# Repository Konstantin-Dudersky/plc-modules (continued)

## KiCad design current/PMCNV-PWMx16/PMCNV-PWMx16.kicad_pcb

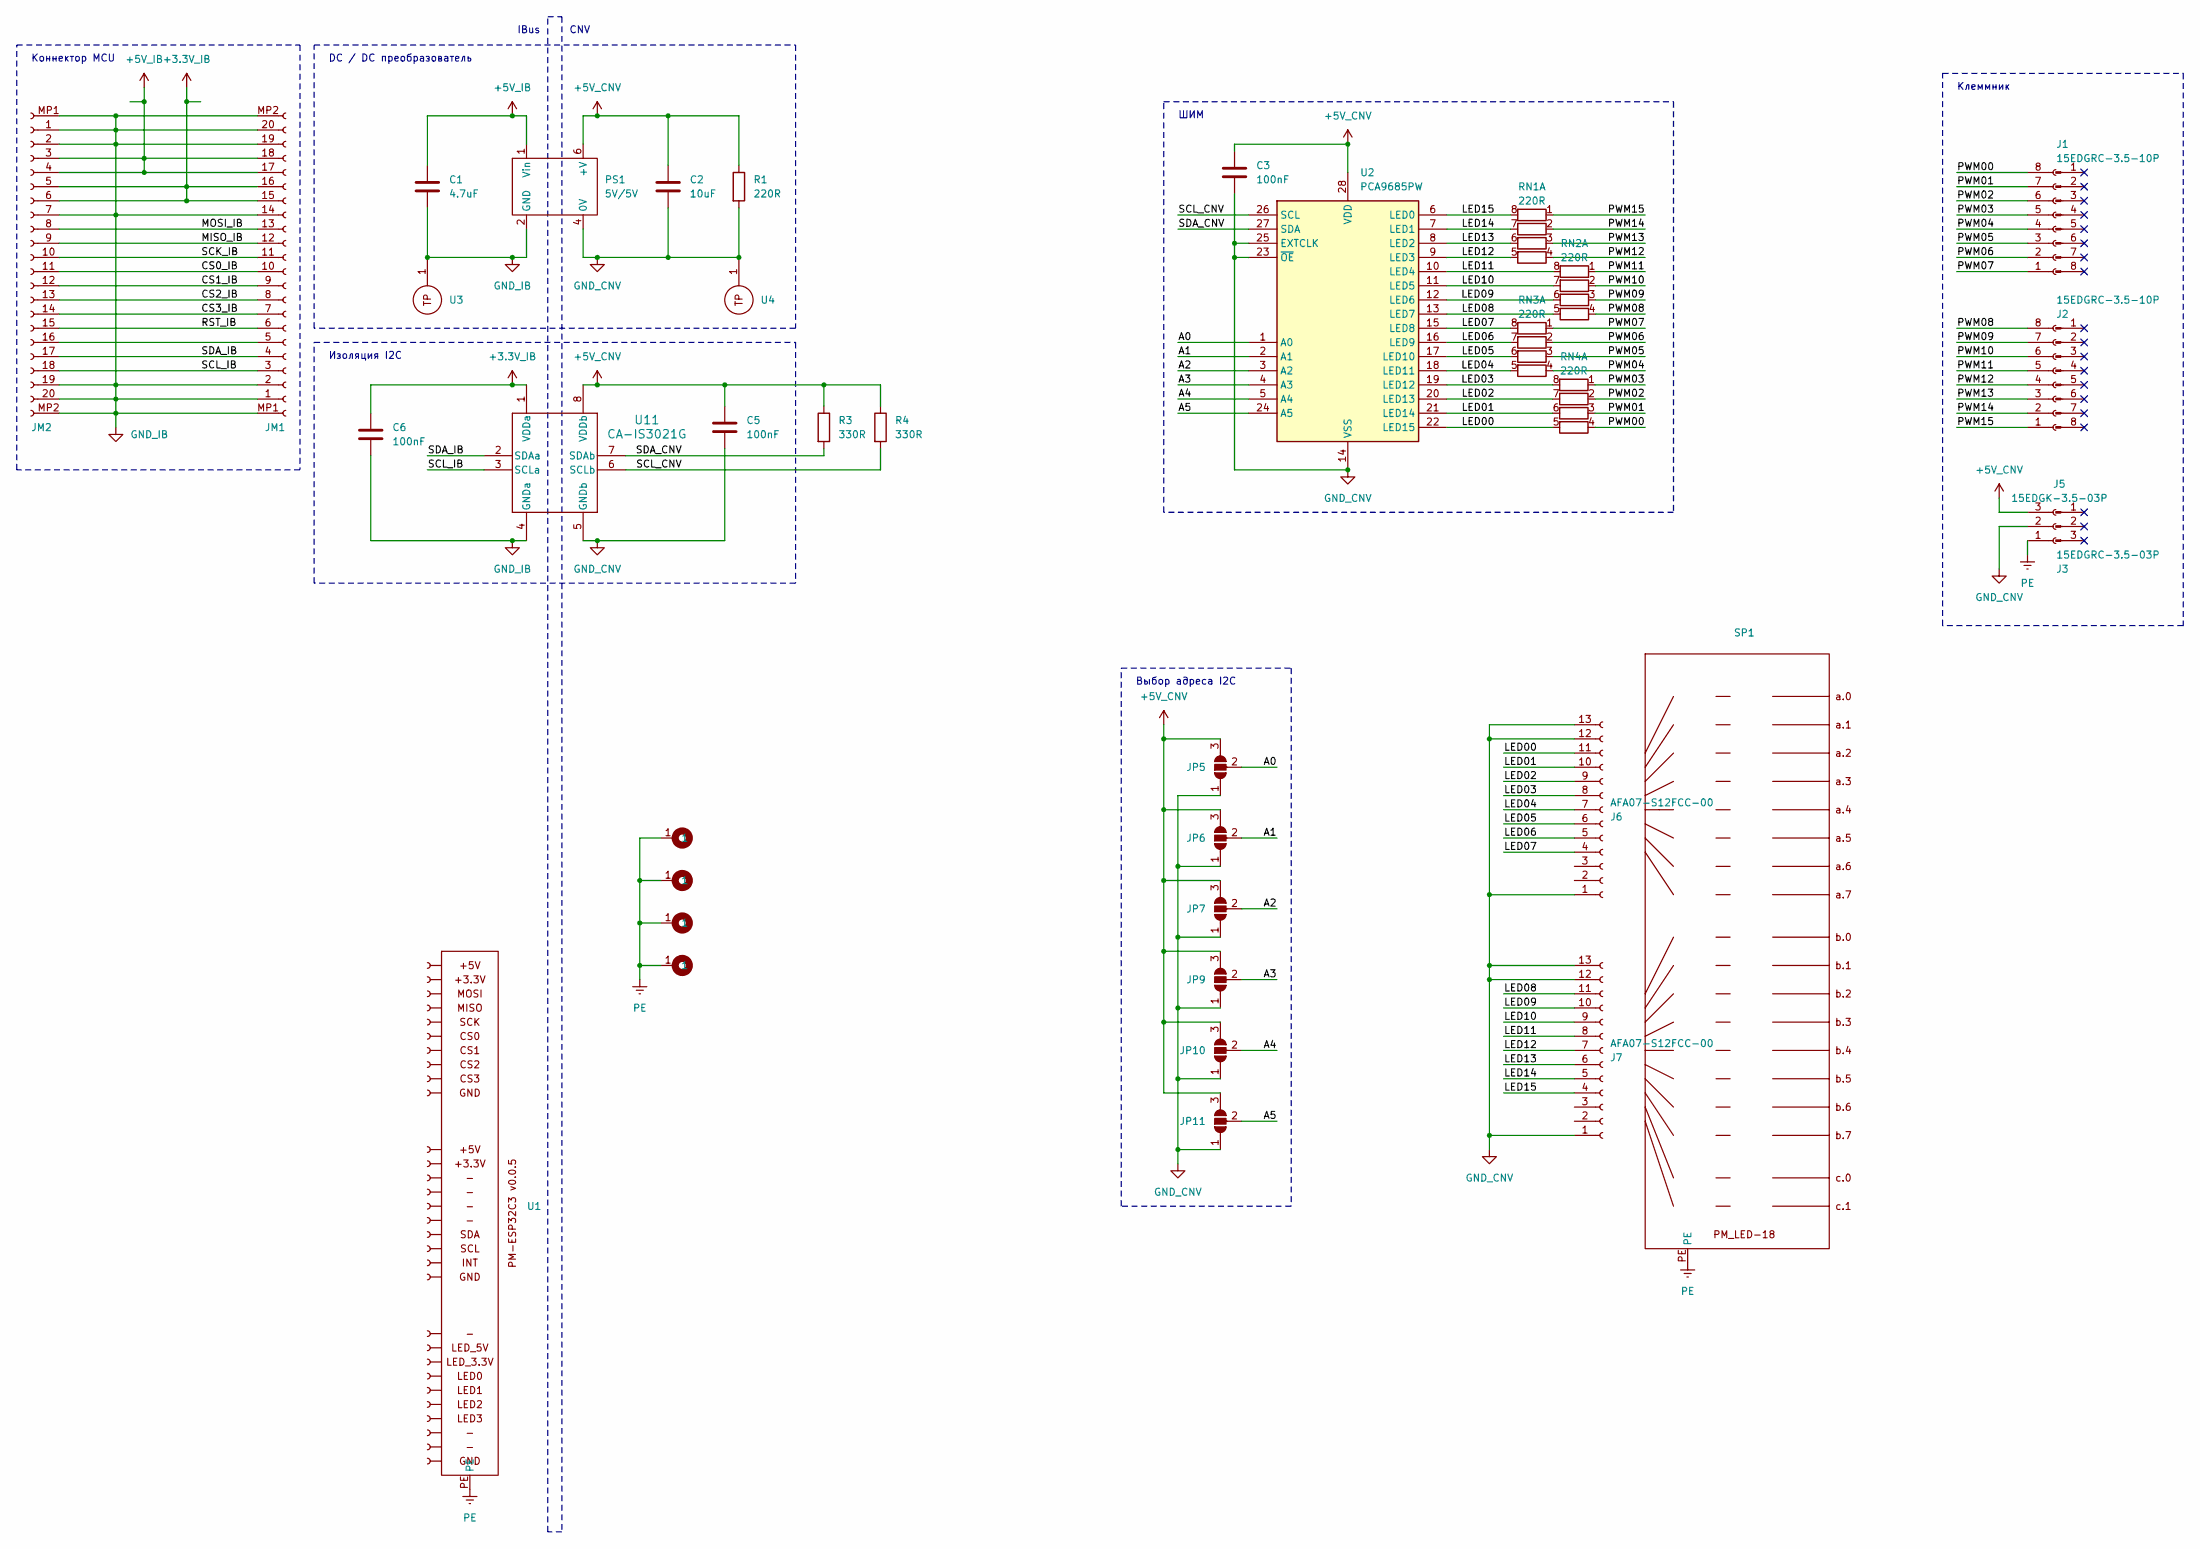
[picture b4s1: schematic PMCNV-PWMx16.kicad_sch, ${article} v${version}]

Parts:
C1: 4.7uF; C_0805_2012Metric; part_ipn C_4.7uF_16V_0805_MLCC-X7R
C2: 10uF; C_0805_2012Metric; part_ipn C_10uF_16V_0805_MLCC-X7R
C3, C5, C6: 100nF; C_0603_1608Metric; part_ipn C_100nF_16V_0603_MLCC-X7R
H1, H2, H3, H4: M4; MountingHole_4.3mm_M4_Pad_Via
J1, J2: 15EDGRC-3.5-10P; 15EDGRC-3.5-08P; part_ipn 15EDGRC-3.5-08P
J3: 15EDGRC-3.5-03P; part_ipn 15EDGRC-3.5-03P
J4, J9: 15EDGK-3.5-10P; part_ipn 15EDGK-3.5-08P
J5: 15EDGK-3.5-03P; part_ipn 15EDGK-3.5-03P
J6, J7: AFA07-S12FCC-00; CONN10_AFA07-S12_JUS; part_ipn AFA07-S12FCC-00
JM1, JM2: AFA07-S20FCC-00; AFA07S20FCA00; part_ipn AFA07-S20FCC-00
JP5, JP6, JP7, JP9, JP10, JP11: SolderJumper_3_Open; SolderJumper-3_P1.3mm_Open_Pad1.0x1.5mm
PS1: 5V/5V; B2405LS-1WR3; part_ipn B0505LS-1W
R1: 220R; R_0603_1608Metric; part_ipn R_220R_0603_1%
R3, R4: 330R; R_0603_1608Metric; part_ipn R_330R_0603_1%
RN1, RN2, RN3, RN4: 220R; R_Array_Convex_4x0603; part_ipn R_220R_0603x4_1%
SP1: PMLED-xx-v0.0.2; part_ipn PMLED-18-v0.0.2
U1: PM-ESP32C3_v0.0.7; part_ipn PM_MCU-ESP32_C3-v0.0.7
U2: PCA9685PW; TSSOP-28_4.4x9.7mm_P0.65mm; part_ipn PCA9685PW
U3, U4: 5117; part_ipn Keystone_5117
U11: CA-IS3021G; SOICW8_CLG; part_ipn CA-IS3021G

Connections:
+3.3V_IB: C6.1, JM1.15 (Pin_11), JM1.16 (Pin_11), JM2.5, JM2.6, U11.1 (VDDa)
+5V_CNV: C2.1, C3.1, C5.1, J3.3, JP5.3 (B), JP6.3 (B), JP7.3 (B), JP9.3 (B), JP10.3 (B), JP11.3 (B), PS1.6 (+V), R1.1, R3.1, R4.1, U2.28 (VDD), U11.8 (VDDb)
+5V_IB: C1.1, JM1.17 (Pin_11), JM1.18 (Pin_11), JM2.3, JM2.4, PS1.1 (Vin)
/A0: JP5.2 (C), U2.1 (A0)
/A1: JP6.2 (C), U2.2 (A1)
/A2: JP7.2 (C), U2.3 (A2)
/A3: JP9.2 (C), U2.4 (A3)
/A4: JP10.2 (C), U2.5 (A4)
/A5: JP11.2 (C), U2.24 (A5)
/CS0_IB: JM1.10, JM2.11
/CS1_IB: JM1.9, JM2.12 (Pin_11)
/CS2_IB: JM1.8, JM2.13 (Pin_11)
/CS3_IB: JM1.7, JM2.14 (Pin_11)
/LED00: J6.11, RN4.5 (R4.2), U2.22 (LED15)
/LED01: J6.10, RN4.6 (R3.2), U2.21 (LED14)
/LED02: J6.9, RN4.7 (R2.2), U2.20 (LED13)
/LED03: J6.8, RN4.8 (R1.2), U2.19 (LED12)
/LED04: J6.7, RN3.5 (R4.2), U2.18 (LED11)
/LED05: J6.6, RN3.6 (R3.2), U2.17 (LED10)
/LED06: J6.5, RN3.7 (R2.2), U2.16 (LED9)
/LED07: J6.4, RN3.8 (R1.2), U2.15 (LED8)
/LED08: J7.11, RN2.5 (R4.2), U2.13 (LED7)
/LED09: J7.10, RN2.6 (R3.2), U2.12 (LED6)
/LED10: J7.9, RN2.7 (R2.2), U2.11 (LED5)
/LED11: J7.8, RN2.8 (R1.2), U2.10 (LED4)
/LED12: J7.7, RN1.5 (R4.2), U2.9 (LED3)
/LED13: J7.6, RN1.6 (R3.2), U2.8 (LED2)
/LED14: J7.5, RN1.7 (R2.2), U2.7 (LED1)
/LED15: J7.4, RN1.8 (R1.2), U2.6 (LED0)
/MISO_IB: JM1.12 (Pin_11), JM2.9
/MOSI_IB: JM1.13 (Pin_11), JM2.8
/PWM00: J1.8, RN4.4 (R4.1)
/PWM01: J1.7, RN4.3 (R3.1)
/PWM02: J1.6, RN4.2 (R2.1)
/PWM03: J1.5, RN4.1 (R1.1)
/PWM04: J1.4, RN3.4 (R4.1)
/PWM05: J1.3, RN3.3 (R3.1)
/PWM06: J1.2, RN3.2 (R2.1)
/PWM07: J1.1, RN3.1 (R1.1)
/PWM08: J2.8, RN2.4 (R4.1)
/PWM09: J2.7, RN2.3 (R3.1)
/PWM10: J2.6, RN2.2 (R2.1)
/PWM11: J2.5, RN2.1 (R1.1)
/PWM12: J2.4, RN1.4 (R4.1)
/PWM13: J2.3, RN1.3 (R3.1)
/PWM14: J2.2, RN1.2 (R2.1)
/PWM15: J2.1, RN1.1 (R1.1)
/RST_IB: JM1.6, JM2.15 (Pin_11)
/SCK_IB: JM1.11, JM2.10
/SCL_CNV: R4.2, U2.26 (SCL), U11.6 (SCLb)
/SCL_IB: JM1.3, JM2.18 (Pin_11), U11.3 (SCLa)
/SDA_CNV: R3.2, U2.27 (SDA), U11.7 (SDAb)
/SDA_IB: JM1.4, JM2.17 (Pin_11), U11.2 (SDAa)
GND_CNV: C2.2, C3.2, C5.2, J3.2, J6.1, J6.12 (Pin_11), J6.13 (Pin_11), J7.1, J7.12 (Pin_11), J7.13 (Pin_11), JP5.1 (A), JP6.1 (A), JP7.1 (A), JP9.1 (A), JP10.1 (A), JP11.1 (A), PS1.4 (0V), R1.2, U2.14 (VSS), U2.23 (~OE), U2.25 (EXTCLK), U4.1, U11.5 (GNDb)
GND_IB: C1.2, C6.2, JM1.1, JM1.2, JM1.14 (Pin_11), JM1.19 (Pin_11), JM1.20 (Pin_11), JM1.MP1 (Pin_11), JM1.MP2 (Pin_11), JM2.1, JM2.2, JM2.7, JM2.19 (Pin_11), JM2.20 (Pin_11), JM2.MP1 (Pin_11), JM2.MP2 (Pin_11), PS1.2 (GND), U3.1, U11.4 (GNDa)
unnamed: JM1.5, JM2.16 (Pin_11)
PE: H1.1, H2.1, H3.1, H4.1, J3.1, SP1.PE, U1.PE

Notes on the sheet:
ШИМ
IBus
DC / DC преобразователь
Клеммник
Выбор адреса I2C
CNV
Коннектор MCU
Изоляция I2C

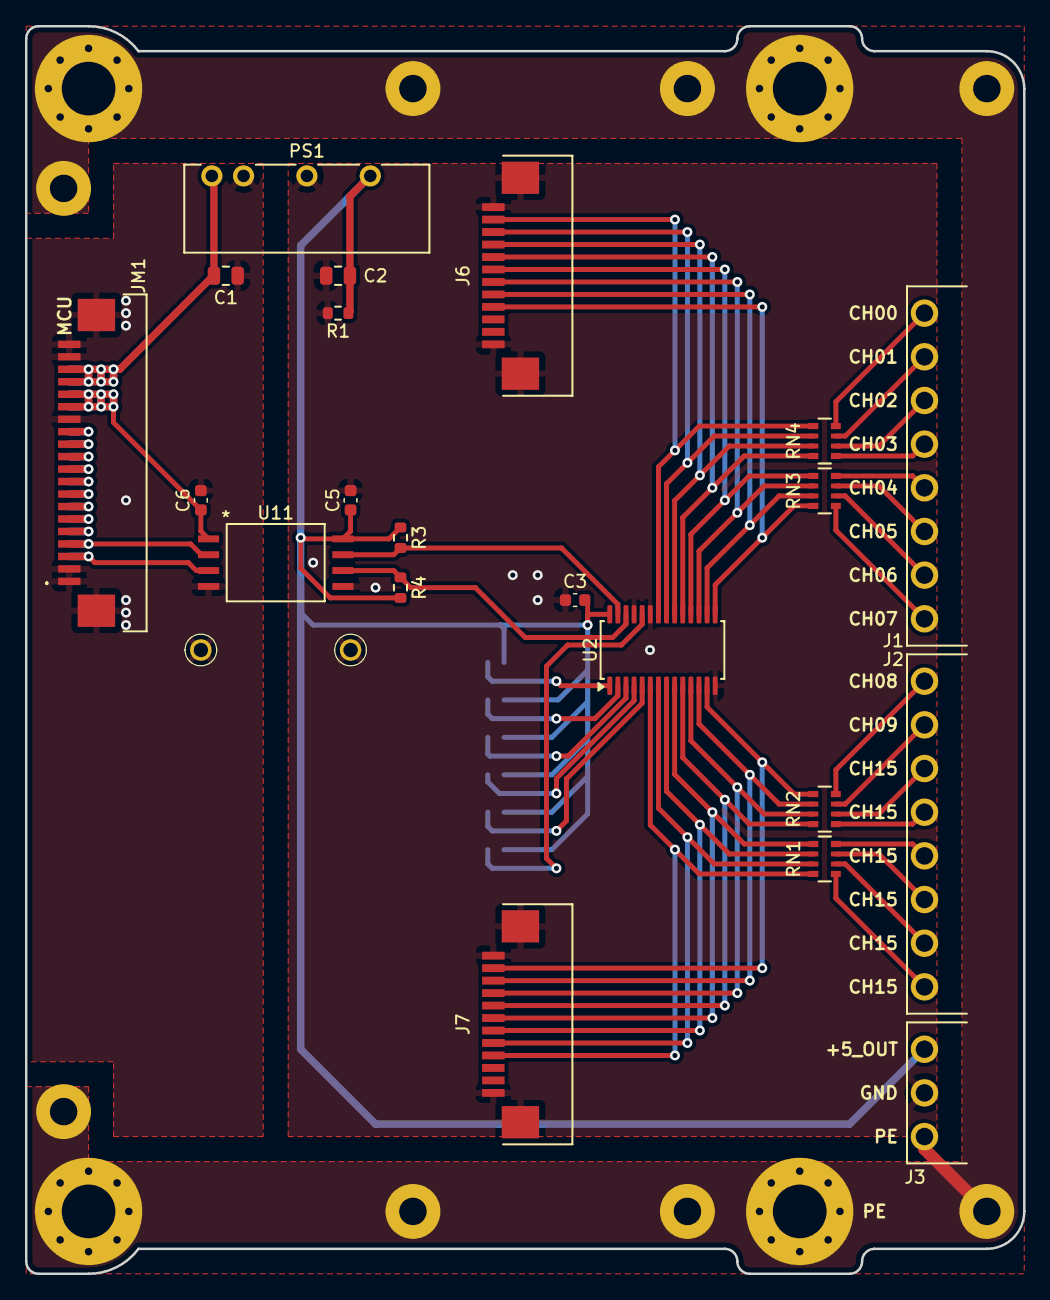
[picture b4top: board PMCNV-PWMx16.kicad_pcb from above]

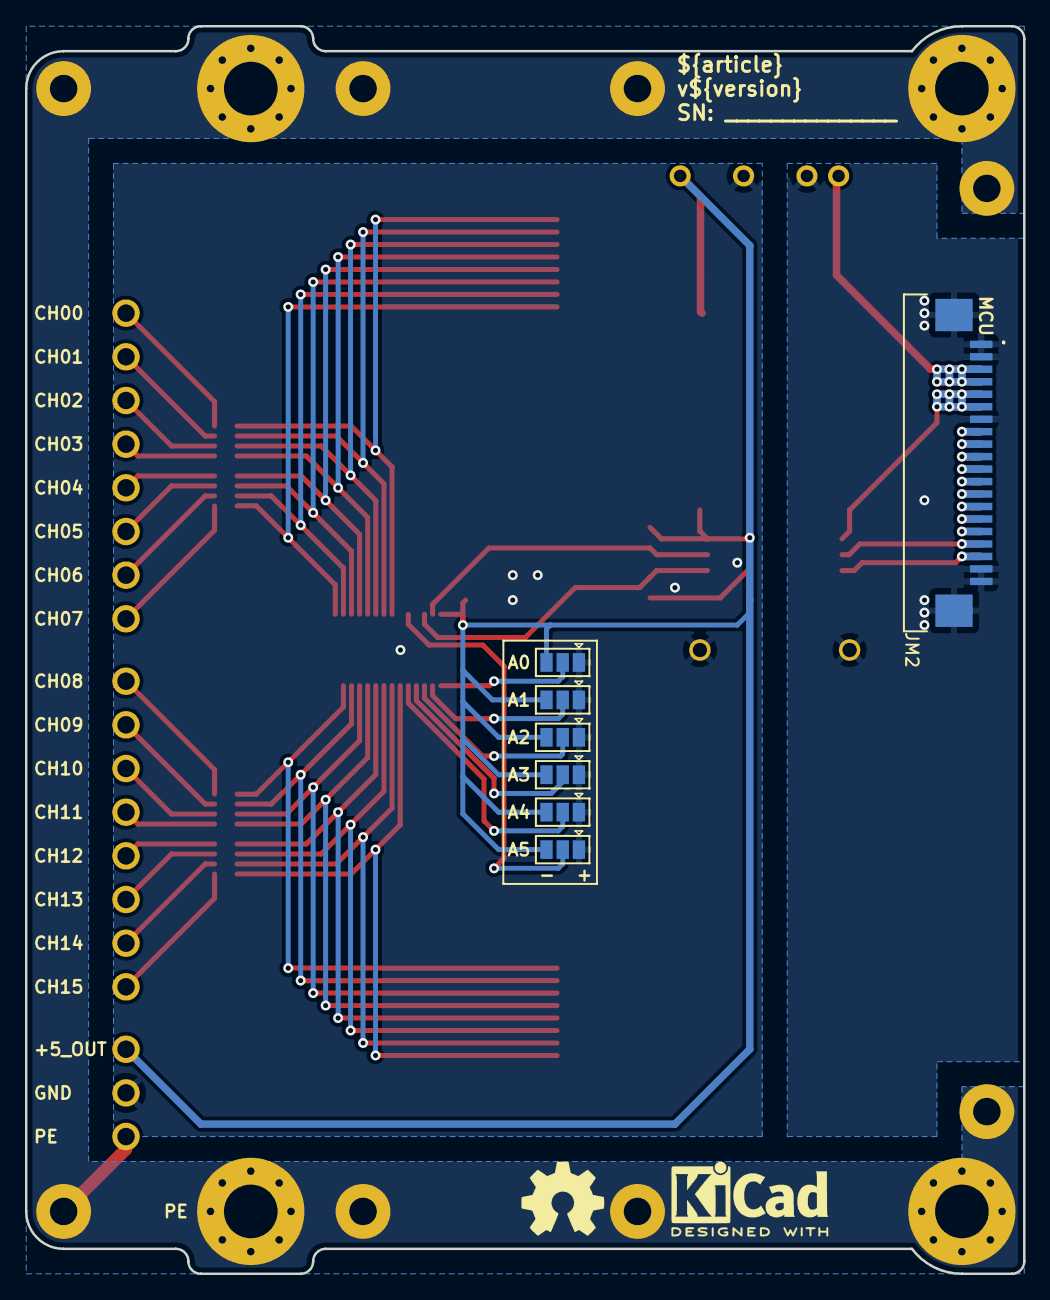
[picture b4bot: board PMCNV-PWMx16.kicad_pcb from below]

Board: 2 copper layers, 80.0 x 100.0 mm, 38 parts (9 on the bottom side), 57 nets.

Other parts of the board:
kicad_logo: KiCad-Logo2_5mm_SilkScreen
oshw_logo: OSHW-Symbol_6.7x6mm_SilkScreen

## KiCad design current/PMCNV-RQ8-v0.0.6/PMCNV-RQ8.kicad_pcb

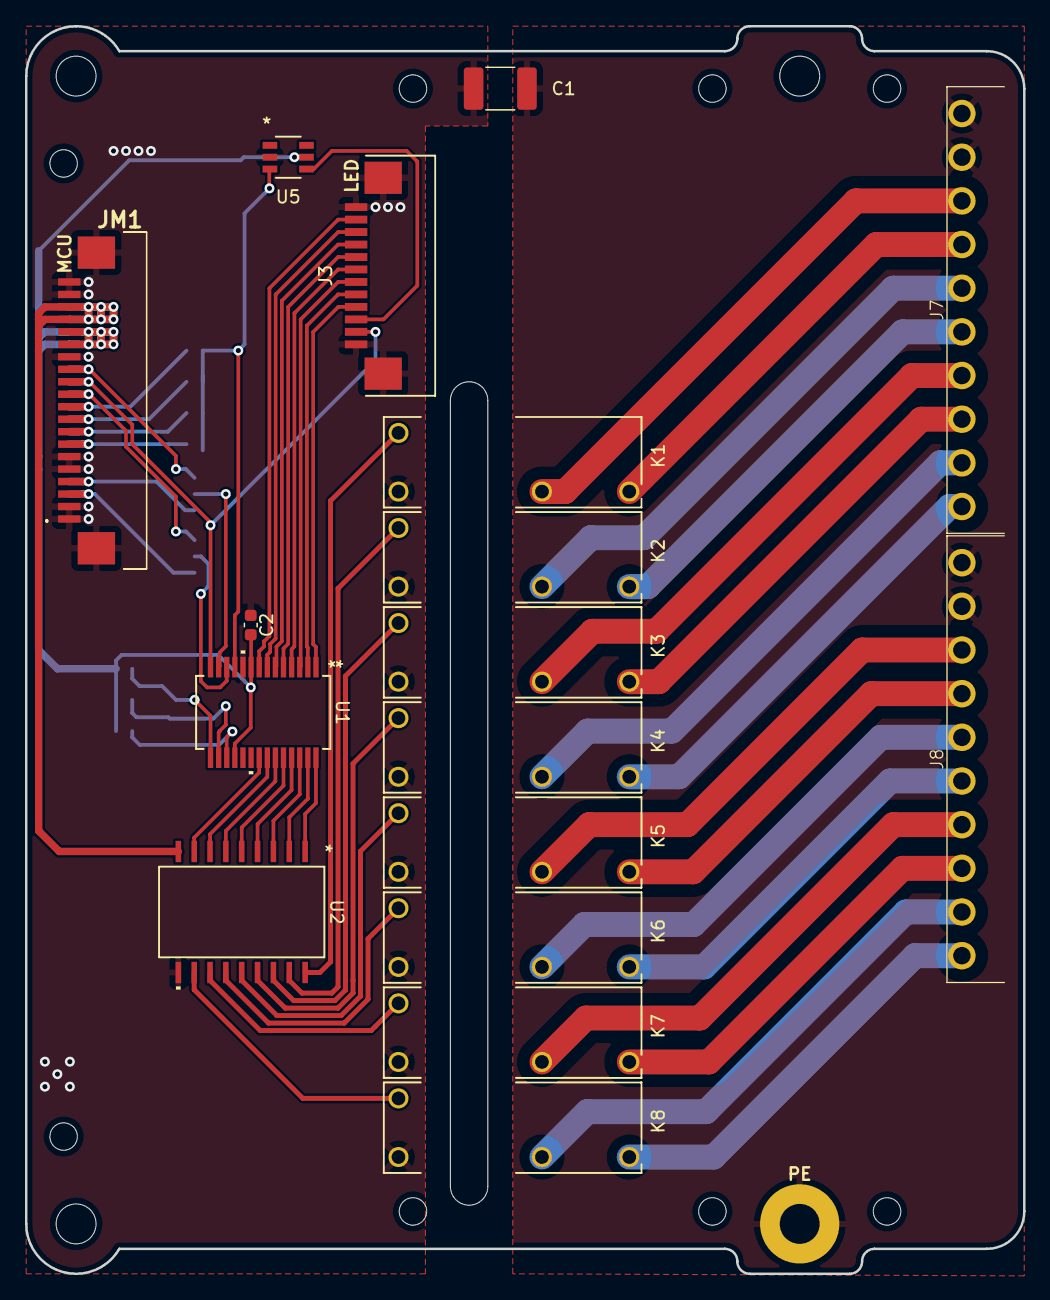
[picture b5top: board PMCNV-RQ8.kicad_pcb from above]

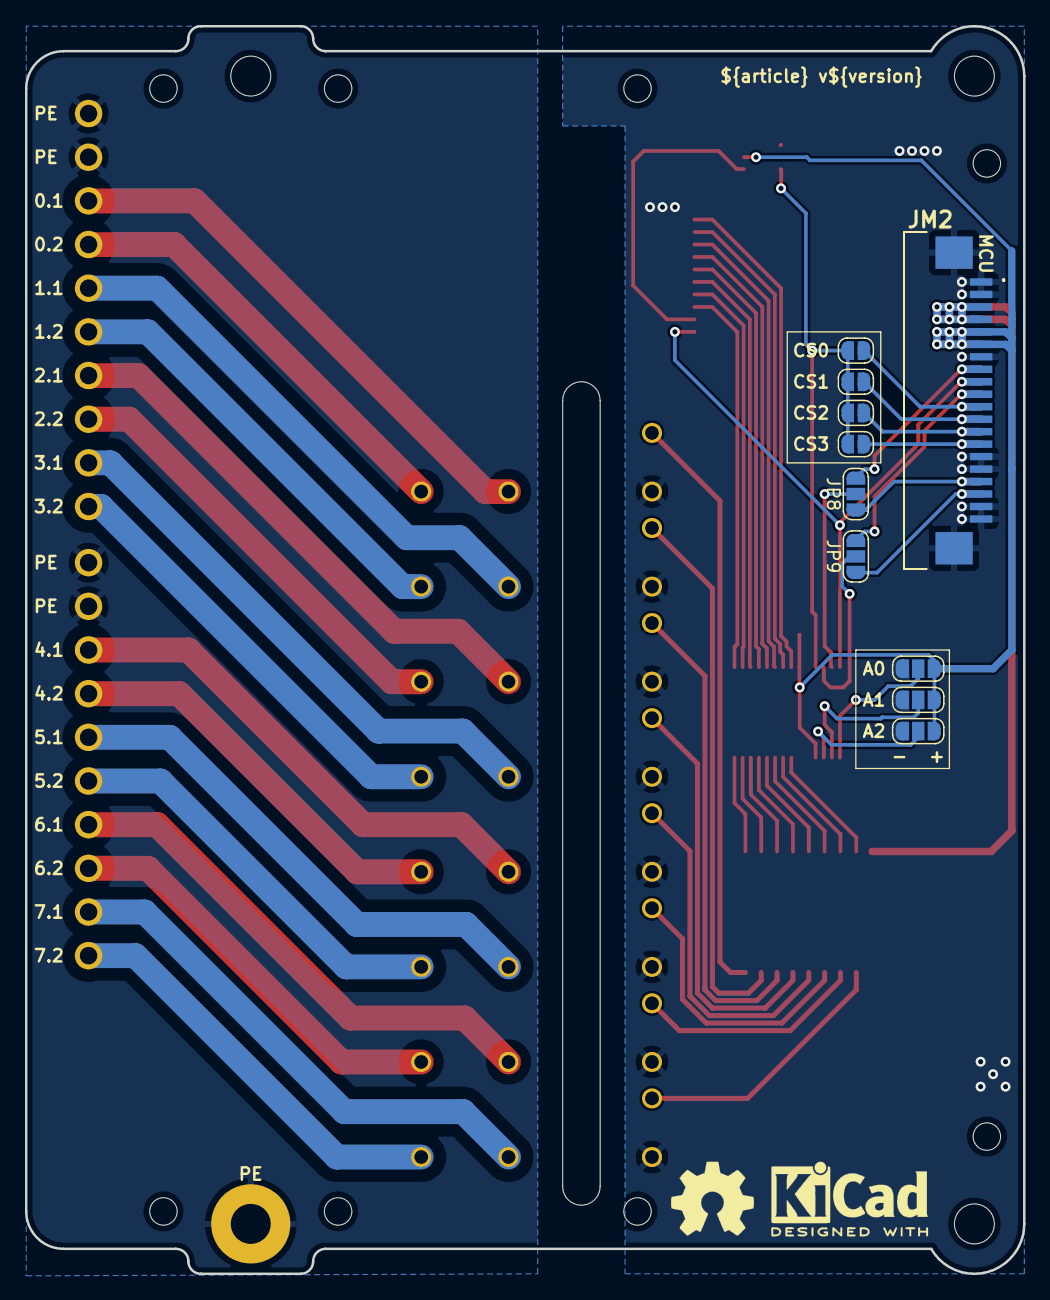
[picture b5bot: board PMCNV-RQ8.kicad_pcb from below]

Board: 2 copper layers, 80.0 x 100.0 mm, 35 parts (12 on the bottom side), 60 nets.

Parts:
C1: 4.7nF 2kV; C_1812_4532Metric_Pad1.57x3.40mm_HandSolder
C2: 100nF; C_0603_1608Metric
H1, H2, H3: MountingHole_M3
J3: AFA07-S12FCC-00; CONN10_AFA07-S12_JUS
J7, J8: 15EDGRC-3.5-10P
JM1, JM2: AFA07-S20FCC-00; AFA07S20FCA00
JP1, JP2, JP3, JP4: SolderJumper_2_Open; SolderJumper-2_P1.3mm_Open_RoundedPad1.0x1.5mm
JP5, JP6, JP7, JP8, JP9: SolderJumper_3_Open; SolderJumper-3_P1.3mm_Open_RoundedPad1.0x1.5mm
K1, K2, K3, K4, K5, K6, K7, K8: G5NB-1A-E-DC5; G5NB-1A-E_DC12_RELAY_G5NB-1A_DC5_OMR
PE1: PE
U1: MCP23S17_SS; SSOP28_MC_MCH
U2: TBD62783AFG; SOP18-P-375-1p27_TOS-M
U3: PM-LED8_v0.0.2; PM_LED-xx-v0.0.1
U4: PM-ESP32C3_v0.0.5
U5: SN74LVC2G14DBVR; DBV6-M
kicad_logo: KiCad-Logo2_5mm_SilkScreen
oshw_logo: OSHW-Symbol_6.7x6mm_SilkScreen

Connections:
+3.3V_MCU: C2.1, JM1.15 (Pin_11), JM1.16 (Pin_11), JM2.5, JM2.6, JP5.3 (B), JP6.3 (B), JP7.3 (B), U1.9 (VDD), U1.18 (~RESET), U5.5 (VCC)
+5V_MCU: JM1.17 (Pin_11), JM1.18 (Pin_11), JM2.3, JM2.4, U2.9 (VCC)
/A0: JP5.2 (C), U1.15 (A0)
/A1: JP6.2 (C), U1.16 (A1)
/A2: JP7.2 (C), U1.17 (A2)
/CS0_MCU: JM1.10, JM2.11, JP1.1 (A)
/CS1_MCU: JM1.9, JM2.12 (Pin_11), JP2.1 (A)
/CS2_MCU: JM1.8, JM2.13 (Pin_11), JP3.1 (A)
/CS3_MCU: JM1.7, JM2.14 (Pin_11), JP4.1 (A)
/CS_LED: J3.3, U5.4 (2Y)
/CS_MCU: JP1.2 (B), JP2.2 (B), JP3.2 (B), JP4.2 (B), U1.11 (~CS), U5.3 (2A)
/K1: K1.4, U2.18 (O1)
/K1_exp: U1.28 (GPA7), U2.1 (I1)
/K1_led: J3.11, U1.8 (GPB7)
/K2: K2.4, U2.17 (O2)
/K2_exp: U1.27 (GPA6), U2.2 (I2)
/K2_led: J3.10, U1.7 (GPB6)
/K3: K3.4, U2.16 (O3)
/K3_exp: U1.26 (GPA5), U2.3 (I3)
/K3_led: J3.9, U1.6 (GPB5)
/K4: K4.4, U2.15 (O4)
/K4_exp: U1.25 (GPA4), U2.4 (I4)
/K4_led: J3.8, U1.5 (GPB4)
/K5: K5.4, U2.14 (O5)
/K5_exp: U1.24 (GPA3), U2.5 (I5)
/K5_led: J3.7, U1.4 (GPB3)
/K6: K6.4, U2.13 (O6)
/K6_exp: U1.23 (GPA2), U2.6 (I6)
/K6_led: J3.6, U1.3 (GPB2)
/K7: K7.4, U2.12 (O7)
/K7_exp: U1.22 (GPA1), U2.7 (I7)
/K7_led: J3.5, U1.2 (GPB1)
/K8: K8.4, U2.11 (O8)
/K8_exp: U1.21 (GPA0), U2.8 (I8)
/K8_led: J3.4, U1.1 (GPB0)
/MISO_MCU: J3.2, JM1.12 (Pin_11), JM2.9, U1.14 (SO)
/MOSI_MCU: JM1.13 (Pin_11), JM2.8, JP8.3 (B)
/SCK_MCU: JM1.11, JM2.10, JP9.3 (B)
/SCL_MCU: JM1.3, JM2.18 (Pin_11), JP9.1 (A)
/SDA_MCU: JM1.4, JM2.17 (Pin_11), JP8.1 (A)
GND_MCU: C1.2, C2.2, J3.1, J3.12 (Pin_11), J3.13 (Pin_11), JM1.1, JM1.2, JM1.5, JM1.6, JM1.14 (Pin_11), JM1.19 (Pin_11), JM1.20 (Pin_11), JM1.MP1 (Pin_11), JM1.MP2 (Pin_11), JM2.1, JM2.2, JM2.7, JM2.15 (Pin_11), JM2.16 (Pin_11), JM2.19 (Pin_11), JM2.20 (Pin_11), JM2.MP1 (Pin_11), JM2.MP2 (Pin_11), JP5.1 (A), JP6.1 (A), JP7.1 (A), K1.1, K2.1, K3.1, K4.1, K5.1, K6.1, K7.1, K8.1, U1.10 (VSS), U2.10 (GND), U5.2 (GND)
unnamed: J7.1, K4.3
unnamed: J7.2, K4.2
unnamed: J7.3, K3.3
unnamed: J7.4, K3.2
unnamed: J7.5, K2.3
unnamed: J7.6, K2.2
unnamed: J7.7, K1.3
unnamed: J7.8, K1.2
unnamed: J8.1, K8.3
unnamed: J8.2, K8.2
unnamed: J8.3, K7.3
unnamed: J8.4, K7.2
unnamed: J8.5, K6.3
unnamed: J8.6, K6.2
unnamed: J8.7, K5.3
unnamed: J8.8, K5.2
unnamed: JP8.2 (C), U1.13 (SI)
unnamed: JP9.2 (C), U1.12 (SCK)
PE: C1.1, J7.9, J7.10, J8.9, J8.10, PE1.1

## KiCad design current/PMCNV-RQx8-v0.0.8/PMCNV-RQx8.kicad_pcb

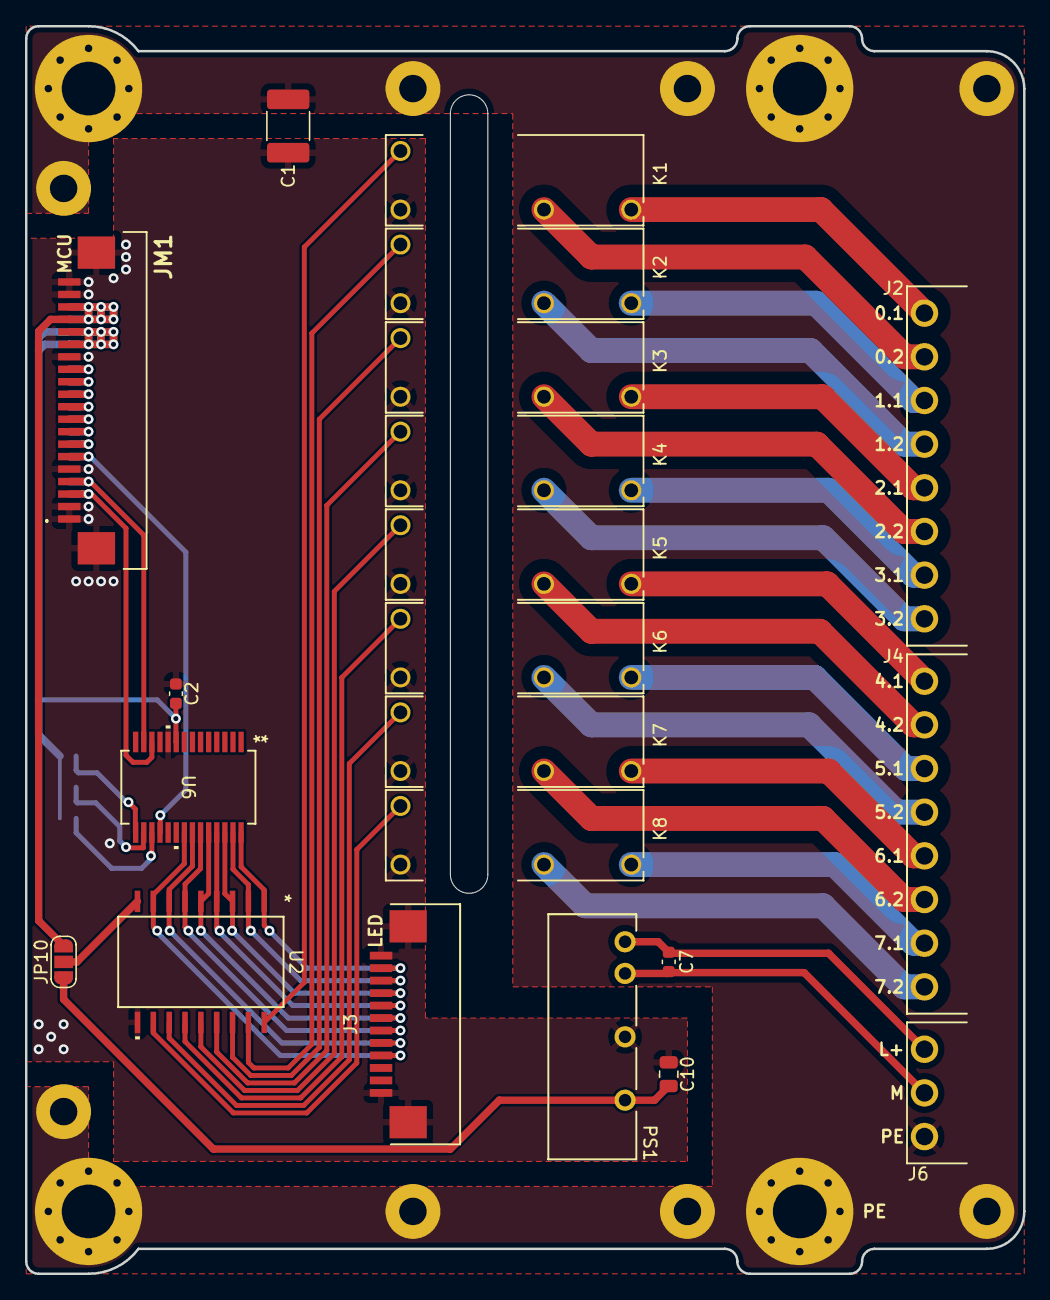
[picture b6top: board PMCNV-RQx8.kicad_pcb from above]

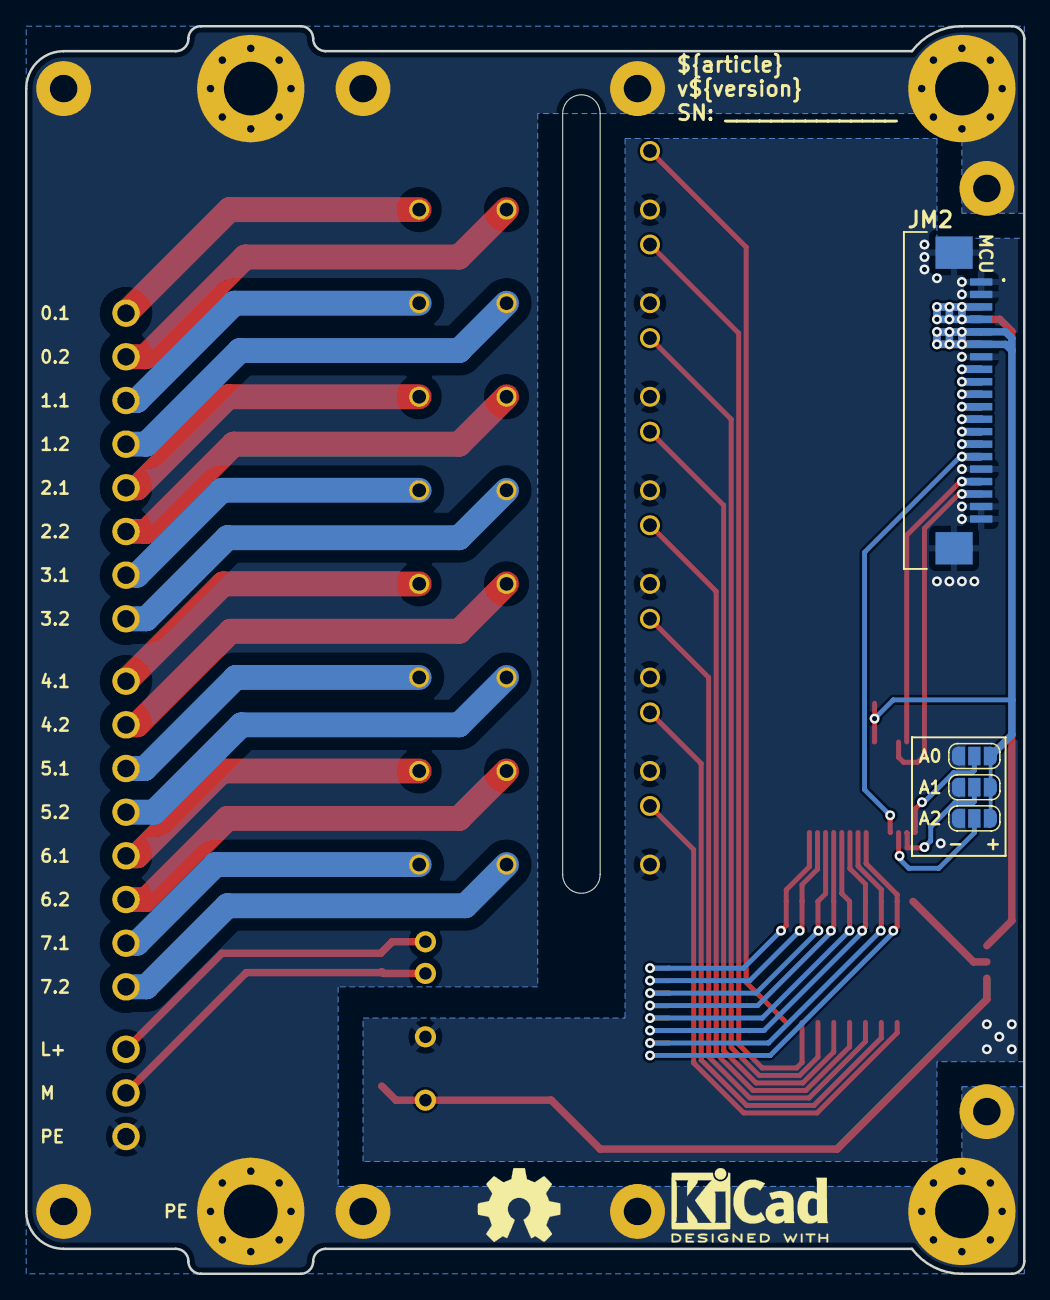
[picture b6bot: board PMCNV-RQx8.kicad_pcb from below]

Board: 2 copper layers, 80.0 x 100.0 mm, 33 parts (7 on the bottom side), 53 nets.

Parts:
C1: 4.7nF 2kV; C_1812_4532Metric_Pad1.57x3.40mm_HandSolder
C2: 100nF; C_0603_1608Metric
C7: 1uF; C_0603_1608Metric
C10: 10uF; C_0805_2012Metric
H1, H2, H3, H4: M4; MountingHole_4.3mm_M4_Pad_Via
J2, J4: 15EDGRC-3.5-08P
J3: AFA07-S12FCC-00; CONN10_AFA07-S12_JUS
J6: 15EDGRC-3.5-05P; 15EDGRC-3.5-03P
JM1, JM2: AFA07-S20FCC-00; AFA07S20FCA00
JP5, JP6, JP7, JP10: SolderJumper_3_Open; SolderJumper-3_P1.3mm_Open_RoundedPad1.0x1.5mm
K1, K2, K3, K4, K5, K6, K7, K8: G5NB-1A-E-DC5; G5NB-1A-E_DC12_RELAY_G5NB-1A_DC5_OMR
PS1: 24V/5V 2W; B2405LS-1WR3
U2: TBD62783AFG; SOP18-P-375-1p27_TOS-M
U3: PM-LED8_v0.0.2; PMLED-xx-v0.0.2
U4: PM-ESP32C3_v0.0.7
U6: MCP23017_SS; SSOP28_MC_MCH
kicad_logo: KiCad-Logo2_5mm_SilkScreen
oshw_logo: OSHW-Symbol_6.7x6mm_SilkScreen

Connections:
+3.3V_MCU: C2.1, JM1.15 (Pin_11), JM1.16 (Pin_11), JM2.5, JM2.6, JP5.3 (B), JP6.3 (B), JP7.3 (B), U6.9 (VDD)
+5V: JP10.2 (C), U2.9 (VCC)
+5V_EXT: C10.1, JP10.1 (A), PS1.6 (+V)
+5V_MCU: JM1.17 (Pin_11), JM1.18 (Pin_11), JM2.3, JM2.4, JP10.3 (B)
+24V_CNV: C7.1, J6.3, PS1.1 (Vin)
/A0: JP5.2 (C), U6.15 (A0)
/A1: JP6.2 (C), U6.16 (A1)
/A2: JP7.2 (C), U6.17 (A2)
/CS0_MCU: JM1.10, JM2.11
/CS1_MCU: JM1.9, JM2.12 (Pin_11)
/CS2_MCU: JM1.8, JM2.13 (Pin_11)
/CS3_MCU: JM1.7, JM2.14 (Pin_11)
/K1: K1.4, U2.18 (O1)
/K1_exp: J3.11, U2.1 (I1), U6.28 (GPA7)
/K2: K2.4, U2.17 (O2)
/K2_exp: J3.10, U2.2 (I2), U6.27 (GPA6)
/K3: K3.4, U2.16 (O3)
/K3_exp: J3.9, U2.3 (I3), U6.26 (GPA5)
/K4: K4.4, U2.15 (O4)
/K4_exp: J3.8, U2.4 (I4), U6.25 (GPA4)
/K5: K5.4, U2.14 (O5)
/K5_exp: J3.7, U2.5 (I5), U6.24 (GPA3)
/K6: K6.4, U2.13 (O6)
/K6_exp: J3.6, U2.6 (I6), U6.23 (GPA2)
/K7: K7.4, U2.12 (O7)
/K7_exp: J3.5, U2.7 (I7), U6.22 (GPA1)
/K8: K8.4, U2.11 (O8)
/K8_exp: J3.4, U2.8 (I8), U6.21 (GPA0)
/MISO_MCU: JM1.12 (Pin_11), JM2.9
/MOSI_MCU: JM1.13 (Pin_11), JM2.8
/RST: JM1.6, JM2.15 (Pin_11), U6.18 (~RESET)
/SCK_MCU: JM1.11, JM2.10
/SCL_MCU: JM1.3, JM2.18 (Pin_11), U6.12 (SCL)
/SDA_MCU: JM1.4, JM2.17 (Pin_11), U6.13 (SDA)
GND_CNV: C7.2, J6.2, PS1.2 (GND)
GND_MCU: C1.2, C2.2, C10.2, J3.1, J3.12 (Pin_11), J3.13 (Pin_11), JM1.1, JM1.2, JM1.5, JM1.14 (Pin_11), JM1.19 (Pin_11), JM1.20 (Pin_11), JM1.MP1 (Pin_11), JM1.MP2 (Pin_11), JM2.1, JM2.2, JM2.7, JM2.16 (Pin_11), JM2.19 (Pin_11), JM2.20 (Pin_11), JM2.MP1 (Pin_11), JM2.MP2 (Pin_11), JP5.1 (A), JP6.1 (A), JP7.1 (A), K1.1, K2.1, K3.1, K4.1, K5.1, K6.1, K7.1, K8.1, PS1.4 (0V), U2.10 (GND), U6.10 (VSS)
unnamed: J2.1, K4.2
unnamed: J2.2, K4.3
unnamed: J2.3, K3.2
unnamed: J2.4, K3.3
unnamed: J2.5, K2.2
unnamed: J2.6, K2.3
unnamed: J2.7, K1.2
unnamed: J2.8, K1.3
unnamed: J4.1, K8.2
unnamed: J4.2, K8.3
unnamed: J4.3, K7.2
unnamed: J4.4, K7.3
unnamed: J4.5, K6.2
unnamed: J4.6, K6.3
unnamed: J4.7, K5.2
unnamed: J4.8, K5.3
PE: C1.1, H1.1, H2.1, H3.1, H4.1, J6.1, U3.PE, U4.PE
